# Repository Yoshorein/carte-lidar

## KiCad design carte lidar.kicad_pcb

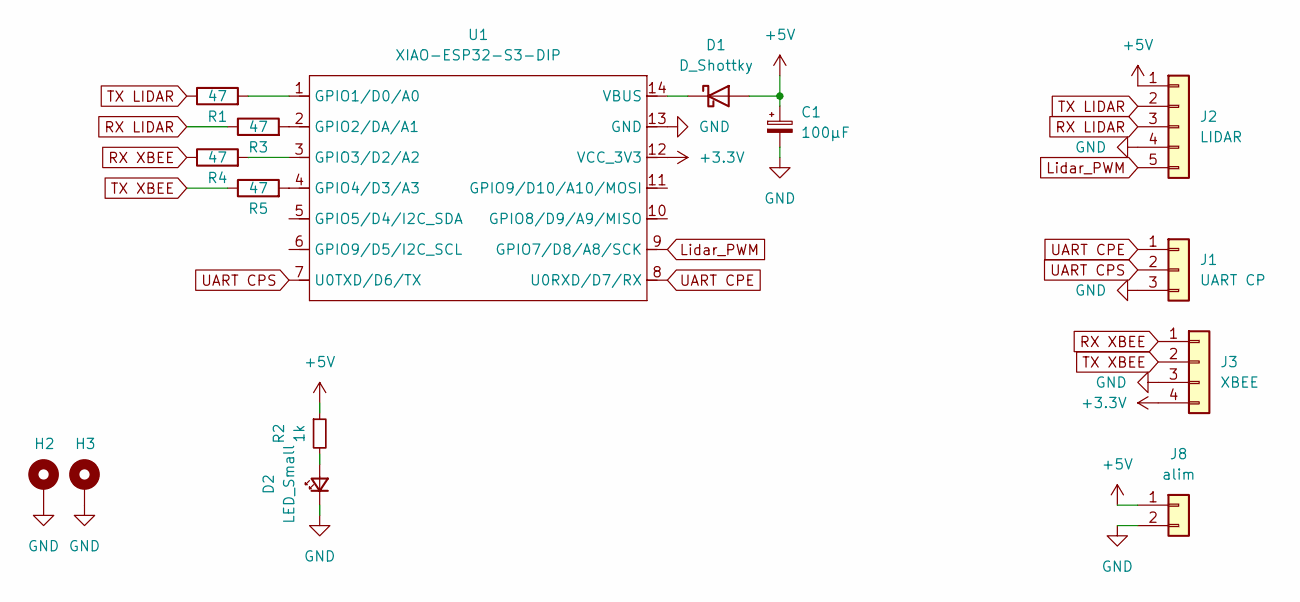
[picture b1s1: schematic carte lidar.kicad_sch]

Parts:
C1: 100µF; CP_Radial_D5.0mm_P2.00mm
D1: D_Shottky; D_DO-41_SOD81_P10.16mm_Horizontal
D2: LED_Small; LED_1206_3216Metric
H2, H3: MountingHole_Pad; MountingHole_3.2mm_M3_Pad_Via
J1: UART CP; Molex_KK-254_AE-6410-03A_1x03_P2.54mm_Vertical
J2: LIDAR; JST_XH_B5B-XH-A_1x05_P2.50mm_Vertical
J3: XBEE; Molex_KK-254_AE-6410-04A_1x04_P2.54mm_Vertical
J8: alim; Molex_KK-254_AE-6410-02A_1x02_P2.54mm_Vertical
R1, R3, R4, R5: 47; R_1206_3216Metric_Pad1.30x1.75mm_HandSolder
R2: 1k; R_1206_3216Metric_Pad1.30x1.75mm_HandSolder
U1: XIAO-ESP32-S3-DIP; XIAO-ESP32S3-DIP

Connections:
+3.3V: J3.4, U1.12 (VCC_3V3)
+5V: C1.1, D1.2 (A), J2.1, J8.1, R2.1
GND: C1.2, D2.1 (K), H2.1, H3.1, J1.3, J2.4, J3.3, J8.2, U1.13 (GND)
Lidar_PWM: J2.5, U1.9 (GPIO7/D8/A8/SCK)
unnamed: D1.1 (K), U1.14 (VBUS)
unnamed: D2.2 (A), R2.2
unnamed: R1.2, U1.1 (GPIO1/D0/A0)
unnamed: R3.2, U1.2 (GPIO2/DA/A1)
unnamed: R4.2, U1.3 (GPIO3/D2/A2)
unnamed: R5.2, U1.4 (GPIO4/D3/A3)
RX LIDAR: J2.3, R3.1
RX XBEE: J3.1, R4.1
TX LIDAR: J2.2, R1.1
TX XBEE: J3.2, R5.1
UART CPE: J1.1, U1.8 (U0RXD/D7/RX)
UART CPS: J1.2, U1.7 (U0TXD/D6/TX)

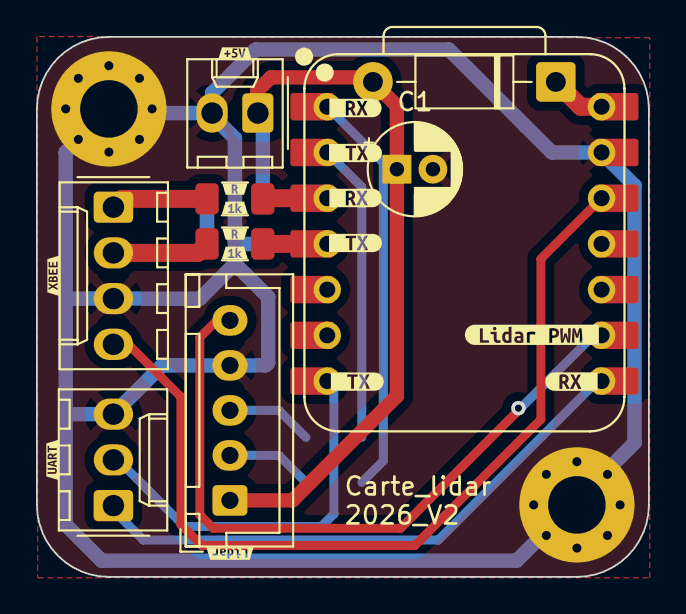
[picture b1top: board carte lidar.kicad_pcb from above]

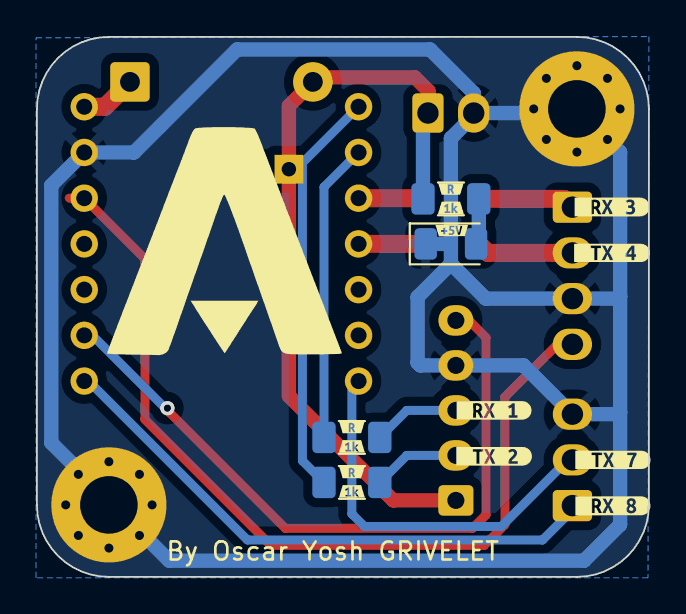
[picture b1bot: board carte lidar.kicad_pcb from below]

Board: 2 copper layers, 34.0 x 30.0 mm, 43 parts (17 on the bottom side), 16 nets.

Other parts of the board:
kibuzzard-690B60FE, kibuzzard-690B60FE#2, kibuzzard-690B60FE#3: G***; kibuzzard-690B60FE
kibuzzard-690B618A, kibuzzard-690B618A#2: G***; kibuzzard-690B618A
kibuzzard-690B6108: G***; kibuzzard-690B6108
kibuzzard-690B6148: G***; kibuzzard-690B6148
kibuzzard-690E93B3: G***; kibuzzard-690E93B3
kibuzzard-690E943A, kibuzzard-690E943A#2, kibuzzard-690E943A#3, kibuzzard-690E943A#4, kibuzzard-690E943A#5: G***; kibuzzard-690E943A
kibuzzard-690E9271: G***; kibuzzard-690E9271
kibuzzard-690E9406, kibuzzard-690E9406#2, kibuzzard-690E9406#3, kibuzzard-690E9406#4, kibuzzard-690E9406#5: G***; kibuzzard-690E9406
kibuzzard-6915AC9B: G***; kibuzzard-6915AC9B
kibuzzard-6915ACBE: G***; kibuzzard-6915ACBE
kibuzzard-6915AD2C: G***; kibuzzard-6915AD2C
kibuzzard-6915AD46: G***; kibuzzard-6915AD46
kibuzzard-6915AD82: G***; kibuzzard-6915AD82
kibuzzard-6915AD88: G***; kibuzzard-6915AD88
kibuzzard-6915ADA8: G***; kibuzzard-6915ADA8
kibuzzard-6915ADB1: G***; kibuzzard-6915ADB1
kibuzzard-6915ADC6: G***; kibuzzard-6915ADC6

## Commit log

2025-10-17 etiquettes
2025-11-03 v2 un poil violent XD
2025-11-05 begining logo
2025-11-09 condo et qq changement
2025-11-12 ayaaaa
2025-11-13 silkscreen
2025-11-25 in case
